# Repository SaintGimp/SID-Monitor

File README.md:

# SID-Monitor

Device for monitoring sudden ionospheric disturbances. Schematic heavily based on work from [Lionel LOUDET](https://sidstation.loudet.org/home-en.xhtml).

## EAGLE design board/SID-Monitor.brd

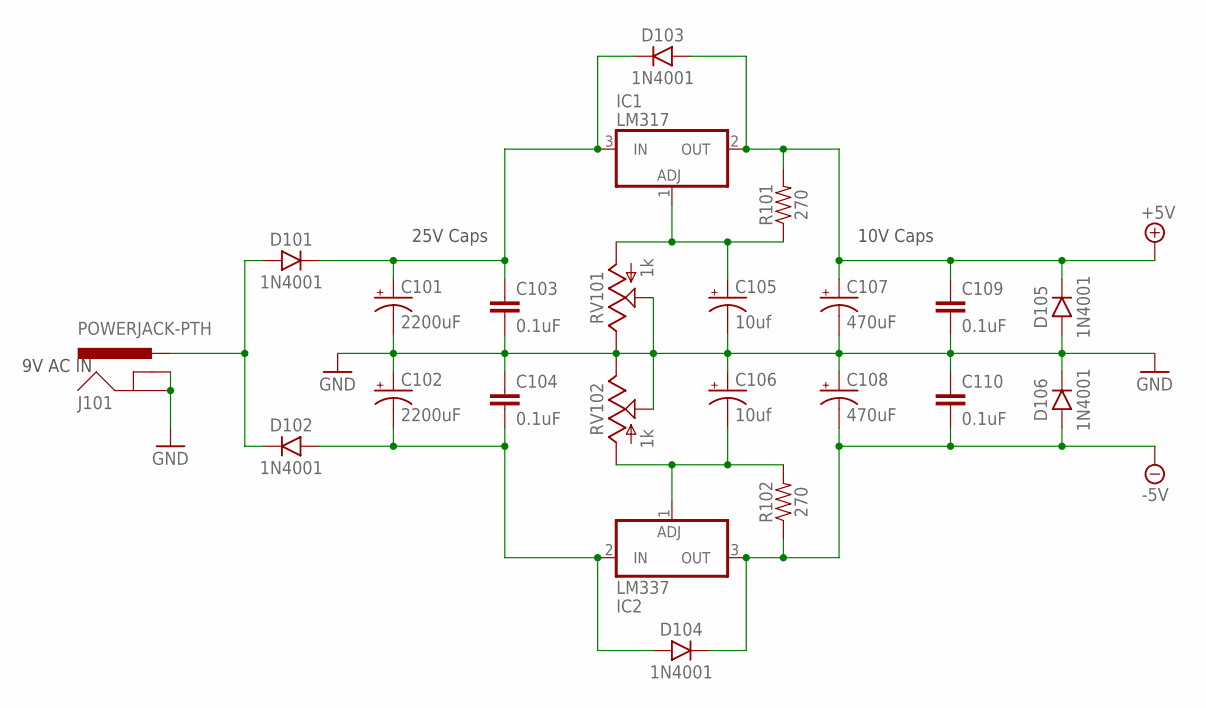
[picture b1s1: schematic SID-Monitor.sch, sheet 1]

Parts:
C101, C102: 2200uF; CAP-POL-5-13
C103, C104, C109, C110: 0.1uF; CAPACITOR-2.5MM
C105, C106: 10uf; CAP-POL-2.5-5
C107, C108: 470uF; CAP-POL-3.5-8
D101, D102, D103, D104, D105, D106: 1N4001; DO-41
IC1: LM317; TO220BV
IC2: LM337; TO220BV
J101: POWERJACK-PTH; POWER_JACK_PTH
R101, R102: 270; AXIAL-7.5MM
RV101, RV102: 1k; TRIM_POT

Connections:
+5V: C107.+, C109.1, D103.1 (+), D105.2 (-), IC1.2 (OUT), R101.P$2 (2); also elsewhere on the board
-5V: C108.-, C110.2, D104.2 (-), D106.1 (+), IC2.3 (OUT), R102.P$1 (1); also elsewhere on the board
GND: C101.-, C102.+, C103.2, C104.1, C105.-, C106.+, C107.-, C108.+, C109.2, C110.1, D105.1 (+), D106.2 (-), J101.GND, J101.GNDBREAK, RV101.1 (S), RV101.2 (E), RV102.1 (S), RV102.2 (E); also elsewhere on the board
unnamed: C102.-, C104.2, D102.1 (+), D104.1 (+), IC2.2 (IN)
unnamed: C101.+, C103.1, D101.2 (-), D103.2 (-), IC1.3 (IN)
unnamed: D101.1 (+), D102.2 (-), J101.PWR
unnamed: C105.+, IC1.1 (ADJ), R101.P$1 (1), RV101.3 (A)
unnamed: C106.-, IC2.1 (ADJ), R102.P$2 (2), RV102.3 (A)

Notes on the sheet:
9V AC IN
25V Caps
10V Caps

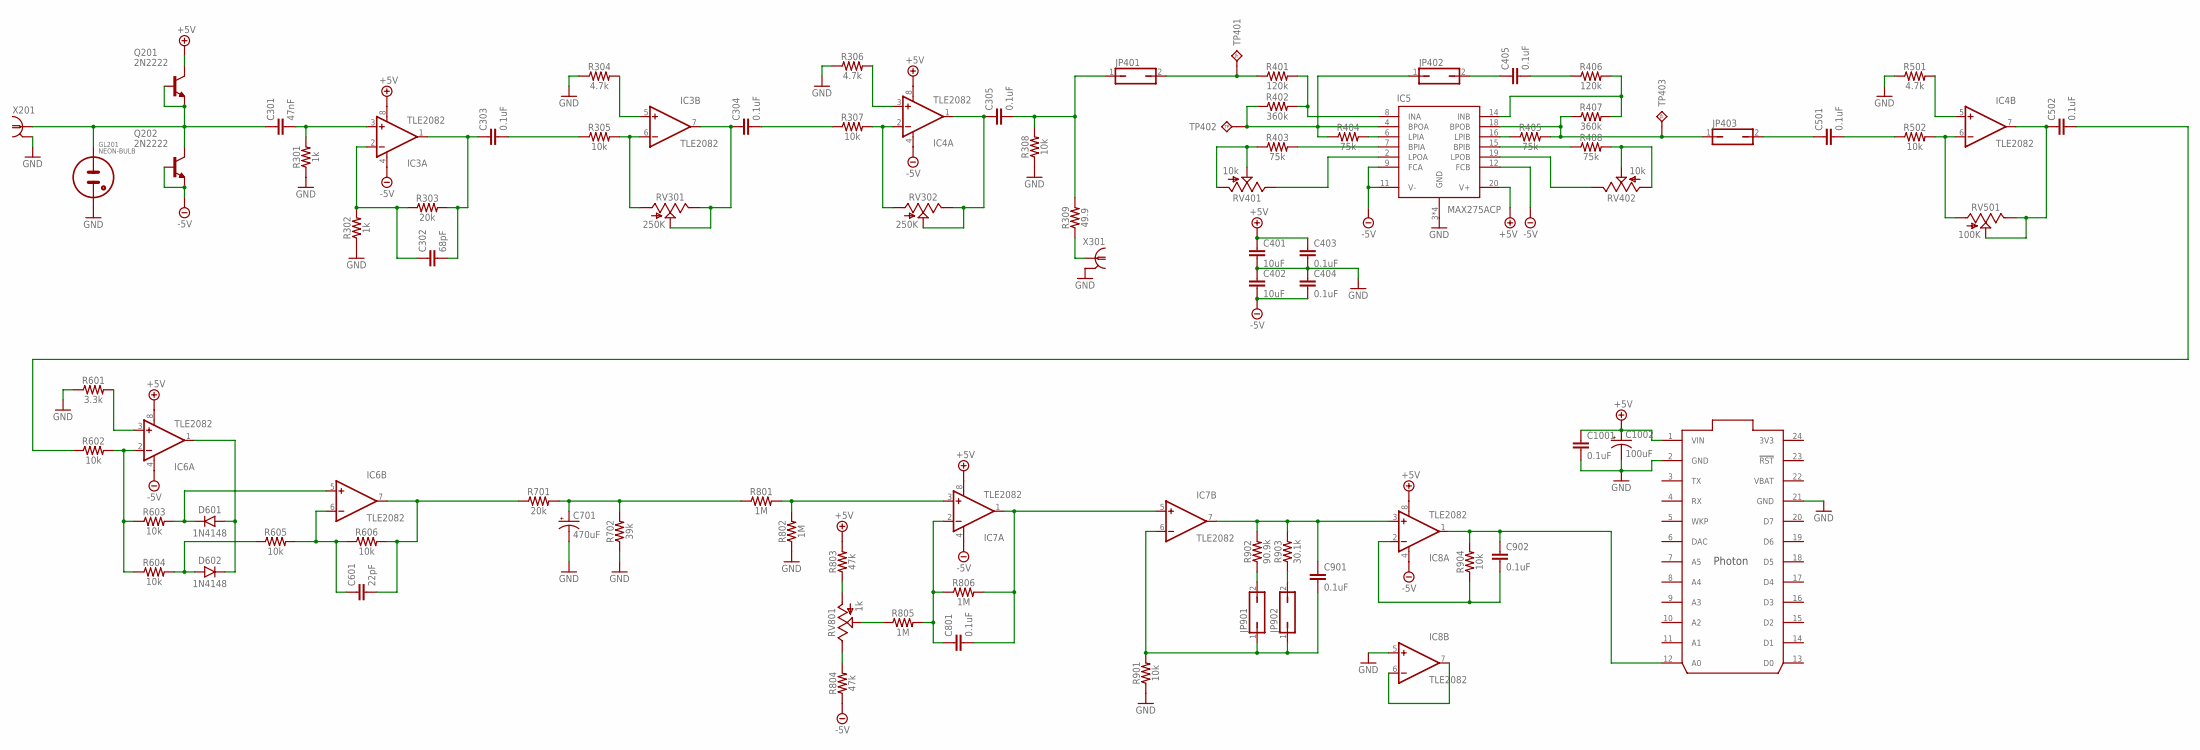
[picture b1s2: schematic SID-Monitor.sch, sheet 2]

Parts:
C301: 47nF; CAPACITOR-2.5MM
C302: 68pF; CAPACITOR-2.5MM
C303, C304, C305, C403, C404, C405, C501, C502, C801, C901, C902, C1001: 0.1uF; CAPACITOR-2.5MM
C401, C402: 10uF; CAPACITOR-5MM
C601: 22pF; CAPACITOR-2.5MM
C701: 470uF; CAP-POL-3.5-8
C1002: 100uF; CAP-POL-3.5-8
D601, D602: 1N4148; DIODE-DO-35
GL201: NEON-BULB
IC3, IC4, IC6, IC7, IC8: TLE2082; DIP08
IC5: MAX275ACP; DIP20
IC9: PHOTON
JP401, JP402, JP403, JP901, JP902: JUMPER1
Q201, Q202: 2N2222; TO92-INLINE
R301, R302: 1k; AXIAL-7.5MM
R303, R701: 20k; AXIAL-7.5MM
R304, R306, R501: 4.7k; AXIAL-7.5MM
R305, R307, R308, R502, R602, R603, R604, R605, R606, R901, R904: 10k; AXIAL-7.5MM
R309: 49.9; AXIAL-7.5MM
R401, R406: 120k; AXIAL-7.5MM
R402, R407: 360k; AXIAL-7.5MM
R403, R404, R405, R408: 75k; AXIAL-7.5MM
R601: 3.3k; AXIAL-7.5MM
R702: 39k; AXIAL-7.5MM
R801, R802, R805, R806: 1M; AXIAL-7.5MM
R803, R804: 47k; AXIAL-7.5MM
R902: 90.9k; AXIAL-7.5MM
R903: 30.1k; AXIAL-7.5MM
RV301, RV302: 250K; TRIM_POT
RV401, RV402: 10k; TRIM_POT
RV501: 100K; TRIM_POT
RV801: 1k; TRIM_POT
TP401, TP402, TP403: TESTPOINT-TH; 1X01
X201, X301: 5414373

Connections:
3V3: IC9.24 (3V3)
+5V: C401.1, C403.1, C1001.1, C1002.+, IC3.8 (V+), IC4.8 (V+), IC5.20 (V+), IC6.8 (V+), IC7.8 (V+), IC8.8 (V+), IC9.1 (VIN), Q201.3 (C), R803.P$2 (2); also elsewhere on the board
-5V: C402.2, C404.2, IC3.4 (V-), IC4.4 (V-), IC5.9 (FCA), IC5.11 (V-), IC5.12 (FCB), IC6.4 (V-), IC7.4 (V-), IC8.4 (V-), Q202.1 (E), Q202.2 (B), R804.P$1 (1); also elsewhere on the board
GND: C401.2, C402.1, C403.2, C404.1, C701.-, C1001.2, C1002.-, GL201.2 (C), IC5.3 (GND), IC5.5 (GND), IC5.10 (GND), IC5.17 (GND), IC8.5 (+IN), IC9.2 (GND), IC9.21 (GND), R301.P$1 (1), R302.P$1 (1), R304.P$1 (1), R306.P$1 (1), R308.P$1 (1), R501.P$1 (1), R601.P$1 (1), R702.P$1 (1), R802.P$1 (1), R901.P$1 (1), X201.1 (2), X201.2, X301.1 (2), X301.2; also elsewhere on the board
unnamed: C301.1, GL201.1 (A), Q201.1 (E), Q201.2 (B), Q202.3 (C), X201.3 (1)
unnamed: C301.2, IC3.3 (+IN), R301.P$2 (2)
unnamed: C302.1, IC3.2 (-IN), R302.P$2 (2), R303.P$1 (1)
unnamed: C303.2, R305.P$1 (1)
unnamed: C302.2, C303.1, IC3.1 (OUT), R303.P$2 (2)
unnamed: IC3.6 (-IN), R305.P$2 (2), RV301.3 (A)
unnamed: IC3.5 (+IN), R304.P$2 (2)
unnamed: C305.2, JP401.1, R308.P$2 (2), R309.P$2 (2)
unnamed: IC5.6 (LPIA), R404.P$2 (2)
unnamed: C304.1, IC3.7 (OUT), RV301.1 (S), RV301.2 (E)
unnamed: C304.2, R307.P$1 (1)
unnamed: IC4.2 (-IN), R307.P$2 (2), RV302.3 (A)
unnamed: IC4.3 (+IN), R306.P$2 (2)
unnamed: C305.1, IC4.1 (OUT), RV302.1 (S), RV302.2 (E)
unnamed: IC5.4 (BPOA), JP402.1, R402.P$1 (1), R404.P$1 (1), TP402.1
unnamed: IC5.8 (INA), R401.P$2 (2), R402.P$2 (2)
unnamed: JP401.2, R401.P$1 (1), TP401.1
unnamed: IC5.7 (BPIA), R403.P$2 (2)
unnamed: R403.P$1 (1), RV401.1 (S), RV401.3 (A)
unnamed: IC5.2 (LPOA), RV401.2 (E)
unnamed: C405.1, JP402.2
unnamed: C405.2, R406.P$1 (1)
unnamed: IC5.16 (LPIB), R405.P$1 (1)
unnamed: IC5.14 (INB), R406.P$2 (2), R407.P$2 (2)
unnamed: IC5.18 (BPOB), JP403.1, R405.P$2 (2), R407.P$1 (1), TP403.1
unnamed: C501.2, R502.P$1 (1)
unnamed: IC5.15 (BPIB), R408.P$1 (1)
unnamed: R408.P$2 (2), RV402.1 (S), RV402.3 (A)
unnamed: IC5.19 (LPOB), RV402.2 (E)
unnamed: IC4.6 (-IN), R502.P$2 (2), RV501.3 (A)
unnamed: IC4.5 (+IN), R501.P$2 (2)
unnamed: C502.1, IC4.7 (OUT), RV501.1 (S), RV501.2 (E)
unnamed: C502.2, R602.P$1 (1)
unnamed: C501.1, JP403.2
unnamed: R309.P$1 (1), X301.3 (1)
unnamed: IC8.6 (-IN), IC8.7 (OUT)
unnamed: R803.P$1 (1), RV801.3 (A)
unnamed: IC6.2 (-IN), R602.P$2 (2), R603.P$1 (1), R604.P$1 (1)
unnamed: IC6.3 (+IN), R601.P$2 (2)
unnamed: D601.A (+), D602.C (-), IC6.1 (OUT)
unnamed: D601.C (-), IC6.5 (+IN), R603.P$2 (2)
unnamed: D602.A (+), R604.P$2 (2), R605.P$1 (1)
unnamed: C701.+, R701.P$2 (2), R702.P$2 (2), R801.P$1 (1)
unnamed: C601.2, IC6.7 (OUT), R606.P$2 (2), R701.P$1 (1)
unnamed: C601.1, IC6.6 (-IN), R605.P$2 (2), R606.P$1 (1)
unnamed: R804.P$2 (2), RV801.2 (E)
unnamed: R805.P$1 (1), RV801.1 (S)
unnamed: C801.1, IC7.2 (-IN), R805.P$2 (2), R806.P$1 (1)
unnamed: IC7.3 (+IN), R801.P$2 (2), R802.P$2 (2)
unnamed: C801.2, IC7.1 (OUT), IC7.5 (+IN), R806.P$2 (2)
unnamed: C901.1, IC7.7 (OUT), IC8.3 (+IN), R902.P$2 (2), R903.P$2 (2)
unnamed: JP902.2, R903.P$1 (1)
unnamed: JP901.2, R902.P$1 (1)
unnamed: C901.2, IC7.6 (-IN), JP901.1, JP902.1, R901.P$2 (2)
unnamed: C902.1, IC8.1 (OUT), IC9.12 (A0), R904.P$2 (2)
unnamed: C902.2, IC8.2 (-IN), R904.P$1 (1)
VBAT: IC9.22 (VBAT)

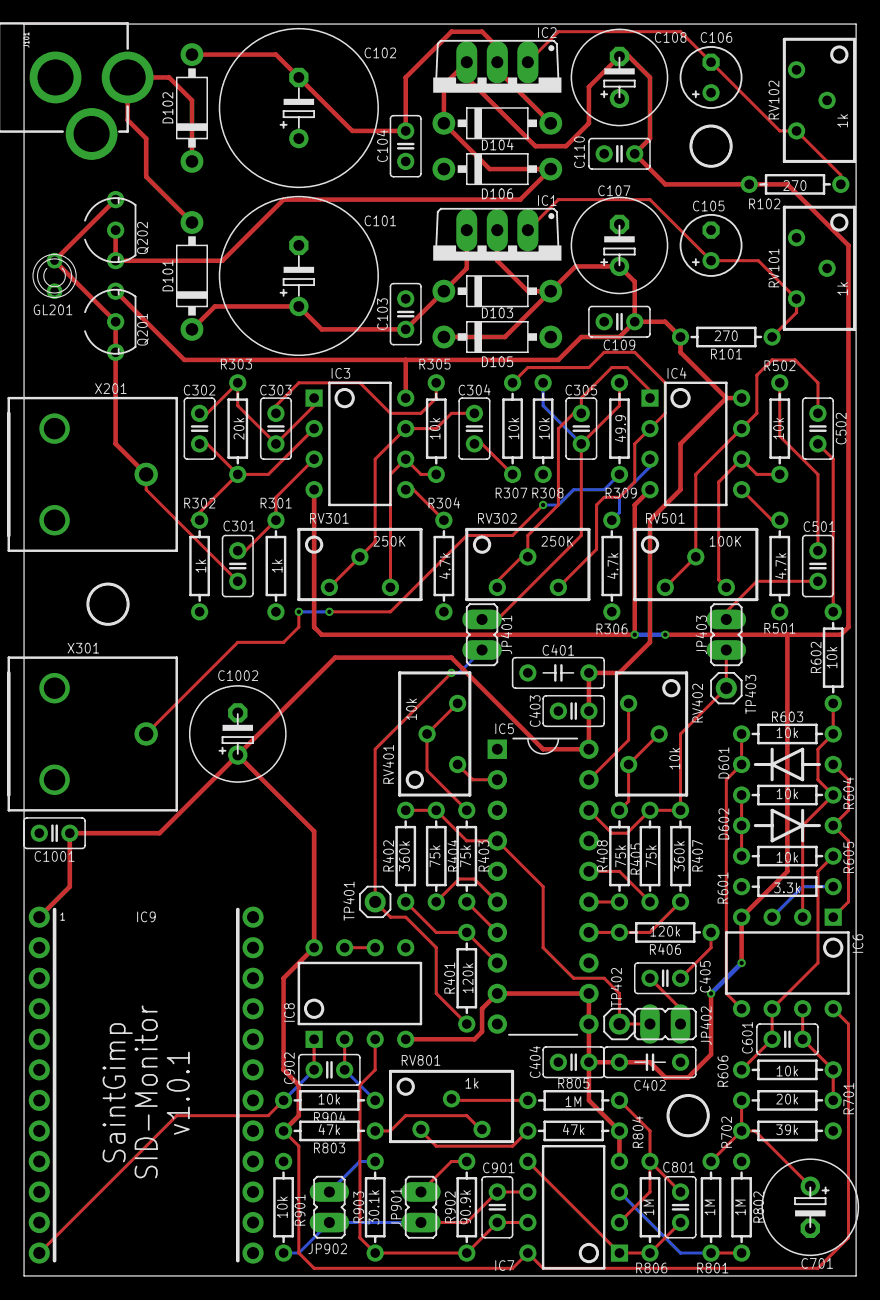
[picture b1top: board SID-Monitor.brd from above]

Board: 2 copper layers, 69.2 x 104.1 mm, 110 parts (0 on the bottom side), 64 nets.

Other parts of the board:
U$1, U$2, U$3: MOUNTING-HOLE-3.2MM

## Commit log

2017-10-28 Initial commit, work in process
2017-11-07 Board layout first pass
2017-11-20 Version 1.0.0 sent out for manufacturing
2017-11-20 Update license and readme
2018-08-27 Update values to tune to 25.2 kHz
2019-04-20 Add device code
2020-01-09 Experimenting with FFT
2022-08-06 V2 WIP
